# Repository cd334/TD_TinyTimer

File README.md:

# TD_TinyTimer
This is a hardware design for [Phobos Lap Timer](https://github.com/phobos-/PhobosLT)

-----------------------------------------------------------------------
Copyright @ Dániel Czigány 2024.

This source describes Open Hardware and is licensed under the CERN-OHL-P v2

You may redistribute and modify this documentation and make products using it under the terms of the CERN-OHL-P v2 (https:/cern.ch/cern-ohl).
This documentation is distributed WITHOUT ANY EXPRESS OR IMPLIED WARRANTY, INCLUDING OF MERCHANTABILITY, SATISFACTORY QUALITY AND FITNESS FOR A PARTICULAR PURPOSE. Please see the CERN-OHL-P v2 for applicable conditions

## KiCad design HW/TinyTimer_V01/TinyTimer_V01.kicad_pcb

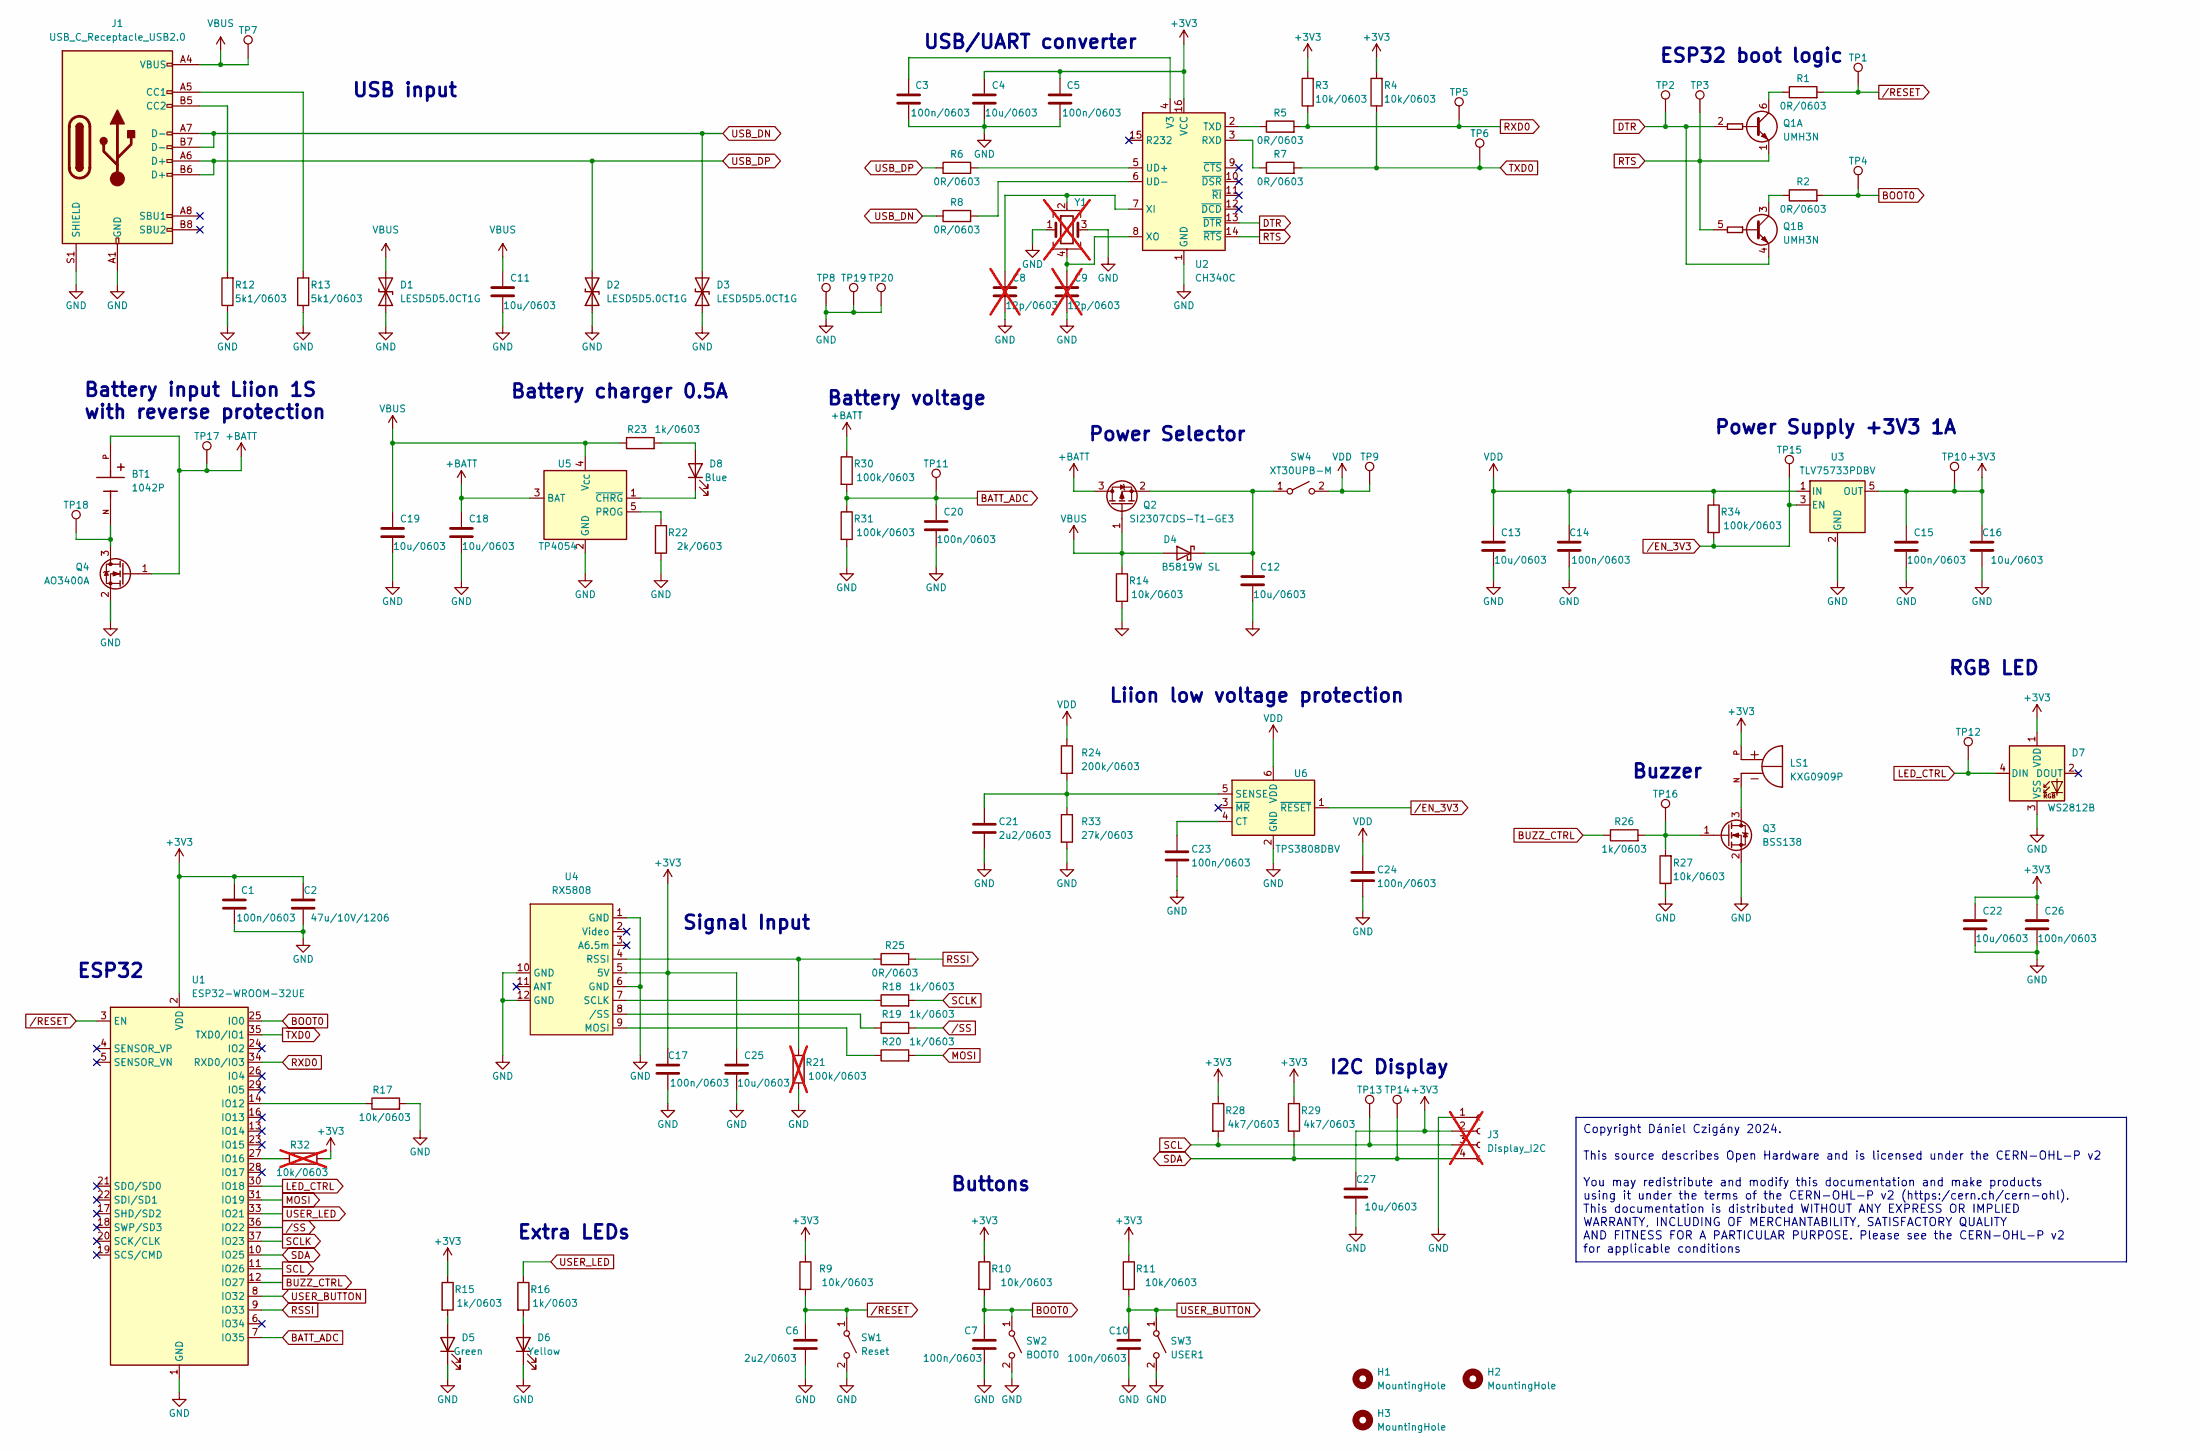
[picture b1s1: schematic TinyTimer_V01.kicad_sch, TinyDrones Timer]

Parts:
BT1: 1042P; BAT_1042P; PARTREV D; LCSC C2988620
C1, C3, C5, C7, C10, C14, C15, C17, C20, C23, C24, C26: 100n/0603; C_0603_1608Metric; LCSC C14663
C2: 47u/10V/1206; C_1206_3216Metric; JLCPCB C96123
C4, C11, C12, C13, C16, C18, C19, C22, C25, C27: 10u/0603; C_0603_1608Metric; LCSC C96446
C6, C21: 2u2/0603; C_0603_1608Metric; LCSC C14663
C8, C9: 12p/0603; C_0603_1608Metric; not fitted
D1, D2, D3: LESD5D5.0CT1G; D_SOD-523; LCSC C383211
D4: B5819W SL; D_SOD-123; LCSC C8598
D5: Green; LED_0603_1608Metric; LCSC C84264
D6: Yellow; LED_0603_1608Metric; LCSC C84265
D7: WS2812B; LED_WS2812B_PLCC4_5.0x5.0mm_P3.2mm; LCSC C2843785
D8: Blue; LED_0603_1608Metric; LCSC C84266
H1, H2, H3: MountingHole; MountingHole_3.5mm
J1: USB_C_Receptacle_USB2.0; USB_C_Receptacle_HRO_TYPE-C-31-M-12; LCSC C2927300
J3: Display_I2C; JST_XH_B4B-XH-A_1x04_P2.50mm_Vertical; not fitted
LS1: KXG0909P; XDCR_KXG0909P; PARTREV 1.1
Q1: UMH3N; SOT-363_SC-70-6; LCSC C62892
Q2: SI2307CDS-T1-GE3; SOT-23; LCSC C141561
Q3: BSS138; SOT-23; LCSC C255592
Q4: AO3400A; SOT-23; LCSC C20917
R1, R2, R5, R6, R7, R8, R25: 0R/0603; R_0603_1608Metric; LCSC C21189
R3, R4, R9, R10, R11, R14, R17, R27: 10k/0603; R_0603_1608Metric; LCSC C25804
R12, R13: 5k1/0603; R_0603_1608Metric; LCSC C23186
R15, R16, R18, R19, R20, R23, R26: 1k/0603; R_0603_1608Metric; LCSC C21190
R21: 100k/0603; R_0603_1608Metric; LCSC C25803; not fitted
R22: 2k/0603; R_0603_1608Metric; LCSC C4190
R24: 200k/0603; R_0603_1608Metric; LCSC C25811
R28, R29: 4k7/0603; R_0603_1608Metric; LCSC C23162
R30, R31, R34: 100k/0603; R_0603_1608Metric; LCSC C25803
R32: 10k/0603; R_0603_1608Metric; LCSC C25804; not fitted
R33: 27k/0603; R_0603_1608Metric; LCSC C22967
SW1: Reset; SW_SPST_B3U-1000P; LCSC C2905189
SW2: BOOT0; SW_SPST_B3U-1000P; LCSC C2905189
SW3: USER1; SW_SPST_B3U-1000P; LCSC C2905189
SW4: XT30UPB-M; PhoenixContact_MCV_1,5_2-G-3.81_1x02_P3.81mm_Vertical
TP1, TP2, TP3, TP4, TP5, TP6, TP7, TP8, TP9, TP10, TP11, TP12, TP13, TP14, TP15, TP16, TP17, TP18: TestPoint; TestPoint_Pad_D1.0mm
TP19, TP20: TestPoint; TestPoint_THTPad_D3.0mm_Drill1.5mm
U1: ESP32-WROOM-32UE; LCSC C701344
U2: CH340C; SOIC-16_3.9x9.9mm_P1.27mm; LCSC C84681
U3: TLV75733PDBV; SOT-23-5; LCSC C485517
U4: RX5808; RX5808_THT
U5: TP4054; TSOT-23-5; LCSC C668215
U6: TPS3808DBV; SOT-23-6; LCSC C19653
Y1: Crystal_GND24; Crystal_SMD_3225-4Pin_3.2x2.5mm; not fitted

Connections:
+3V3: C1.1, C2.1, C4.1, C5.1, C15.1, C16.1, C17.1, C22.1, C25.1, C26.1, C27.1, D7.1 (VDD), J3.2, LS1.P, R3.2, R4.2, R9.1, R10.1, R11.1, R15.1, R28.1, R29.1, R32.2, TP10.1, U1.2 (VDD), U2.16 (VCC), U3.5 (OUT), U4.5 (5V)
+BATT: BT1.P, C18.1, Q2.3 (D), Q4.1 (G), R30.1, TP17.1, U5.3 (BAT)
BATT_ADC: C20.1, R30.2, R31.1, TP11.1, U1.7 (IO35)
BOOT0: C7.1, R2.2, R10.2, SW2.1 (A), TP4.1, U1.25 (IO0)
BUZZ_CTRL: R26.1, U1.12 (IO27)
DTR: Q1.2 (B1), Q1.4 (E2), TP2.1, U2.13 (~DTR)
GND: C1.2, C2.2, C3.2, C4.2, C5.2, C6.2, C7.2, C8.2, C9.2, C10.2, C11.2, C12.2, C13.2, C14.2, C15.2, C16.2, C17.2, C18.2, C19.2, C20.2, C21.2, C22.2, C23.2, C24.2, C25.2, C26.2, C27.2, D1.1 (A1), D2.1 (A1), D3.1 (A1), D5.1 (K), D6.1 (K), D7.3 (VSS), J1.A1 (GND), J1.A12 (GND), J1.B1 (GND), J1.B12 (GND), J1.S1 (SHIELD), J3.1, Q3.2 (S), Q4.2 (S), R12.1, R13.1, R14.2, R17.2, R21.2, R22.2, R27.1, R31.2, R33.2, SW1.2 (B), SW2.2 (B), SW3.2 (B), TP8.1, TP19.1, TP20.1, U1.1 (GND), U1.15 (GND), U1.38 (GND), U1.39 (GND), U2.1 (GND), U3.2 (GND), U4.1 (GND), U4.6 (GND), U4.10 (GND), U4.12 (GND), U5.2 (GND), U6.2 (GND), Y1.1, Y1.3
LED_CTRL: D7.4 (DIN), TP12.1, U1.30 (IO18)
MOSI: R20.2, U1.31 (IO19)
unnamed: C12.1, D4.1 (K), Q2.2 (S), SW4.1 (A)
unnamed: D5.2 (A), R15.2
unnamed: D6.2 (A), R16.2
unnamed: D8.2 (A), R23.2
unnamed: D8.1 (K), U5.1 (~CHRG)
unnamed: J1.A5 (CC1), R13.2
unnamed: J1.B5 (CC2), R12.2
unnamed: Q1.6 (C1), R1.1
unnamed: Q1.3 (C2), R2.1
unnamed: LS1.N, Q3.3 (D)
unnamed: Q3.1 (G), R26.2, R27.2, TP16.1
unnamed: BT1.N, Q4.3 (D), TP18.1
unnamed: R17.1, U1.14 (IO12)
unnamed: R32.1, U1.27 (IO16)
unnamed: R7.1, U2.3 (RXD)
unnamed: R5.1, U2.2 (TXD)
unnamed: R6.2, U2.5 (UD+)
unnamed: R8.2, U2.6 (UD-)
unnamed: C3.1, U2.4 (V3)
unnamed: C8.1, U2.7 (XI), Y1.2
unnamed: C9.1, U2.8 (XO), Y1.4
unnamed: R20.1, U4.9 (MOSI)
unnamed: R21.1, R25.1, U4.4 (RSSI)
unnamed: R18.1, U4.7 (SCLK)
unnamed: R19.1, U4.8 (/SS)
unnamed: R22.1, U5.5 (PROG)
unnamed: C23.1, U6.4 (CT)
unnamed: C21.1, R24.2, R33.1, U6.5 (SENSE)
RSSI: R25.2, U1.9 (IO33)
RTS: Q1.1 (E1), Q1.5 (B2), TP3.1, U2.14 (~RTS)
RXD0: R3.1, R5.2, TP5.1, U1.34 (RXD0/IO3)
SCL: J3.3, R28.2, TP13.1, U1.11 (IO26)
SCLK: R18.2, U1.37 (IO23)
SDA: J3.4, R29.2, TP14.1, U1.10 (IO25)
TXD0: R4.1, R7.2, TP6.1, U1.35 (TXD0/IO1)
USB_DN: D3.2 (A2), J1.A7 (D-), J1.B7 (D-), R8.1
USB_DP: D2.2 (A2), J1.A6 (D+), J1.B6 (D+), R6.1
USER_BUTTON: C10.1, R11.2, SW3.1 (A), U1.8 (IO32)
USER_LED: R16.1, U1.33 (IO21)
VBUS: C11.1, C19.1, D1.2 (A2), D4.2 (A), J1.A4 (VBUS), J1.A9 (VBUS), J1.B4 (VBUS), J1.B9 (VBUS), Q2.1 (G), R14.1, R23.1, TP7.1, U5.4 (V_{CC})
VDD: C13.1, C14.1, C24.1, R24.1, R34.1, SW4.2 (B), TP9.1, U3.1 (IN), U6.6 (VDD)
/EN_3V3: R34.2, TP15.1, U3.3 (EN), U6.1 (~RESET)
/RESET: C6.1, R1.2, R9.2, SW1.1 (A), TP1.1, U1.3 (EN)
/SS: R19.2, U1.36 (IO22)

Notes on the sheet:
Copyright Dániel Czigány 2024. This source describes Open Hardware and is licensed under the CERN-OHL-P v2 You may redistribute and modify this documentation and make products using it under the terms of the CERN-OHL-P v2 (https:/cern.ch/cern-ohl). This documentation is distributed WITHOUT ANY EXPR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
Power Supply +3V3 1A
ESP32
Battery input Liion 1S with reverse protection
USB input
Extra LEDs
Buttons
Battery charger 0.5A
Liion low voltage protection
I2C Display
RGB LED
Buzzer
Battery voltage
Signal Input
USB/UART converter
Power Selector
ESP32 boot logic

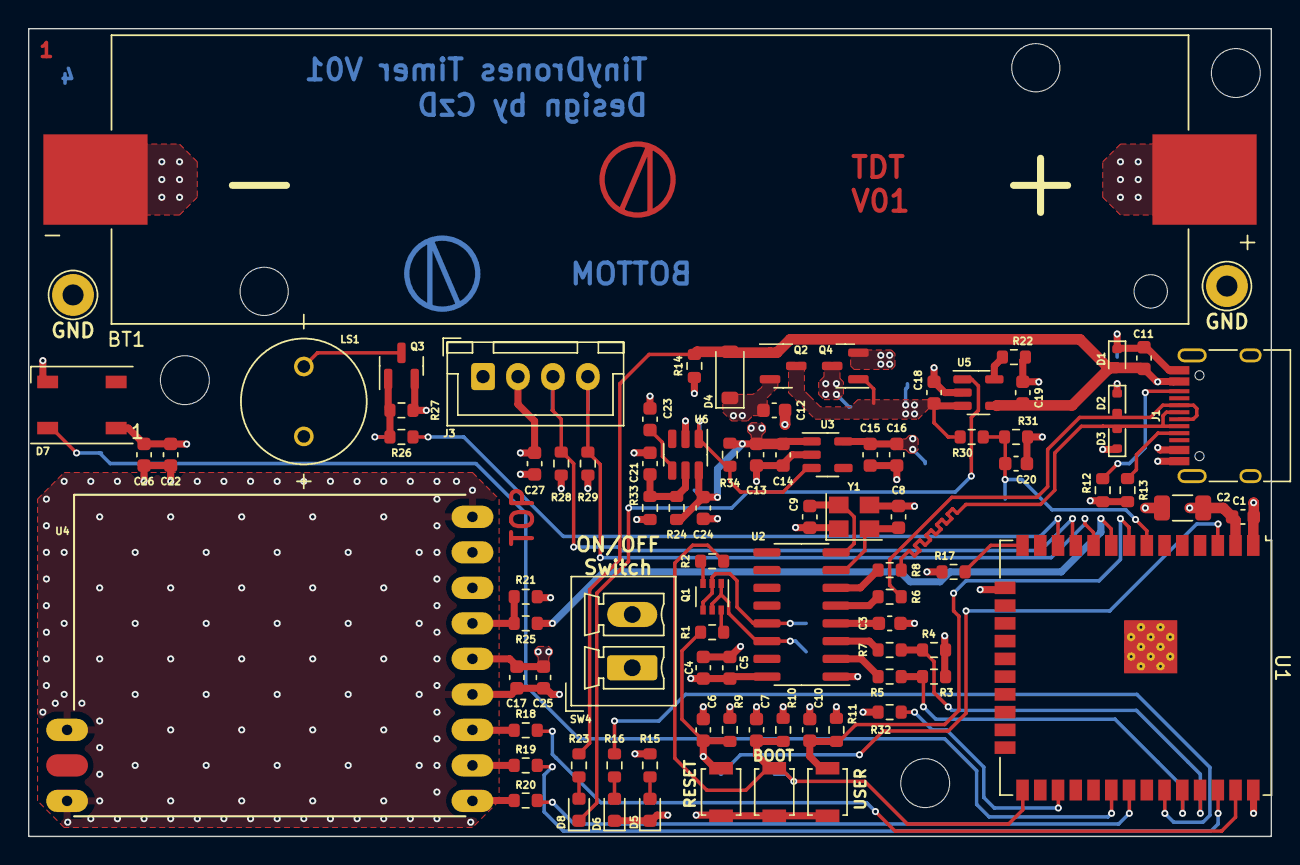
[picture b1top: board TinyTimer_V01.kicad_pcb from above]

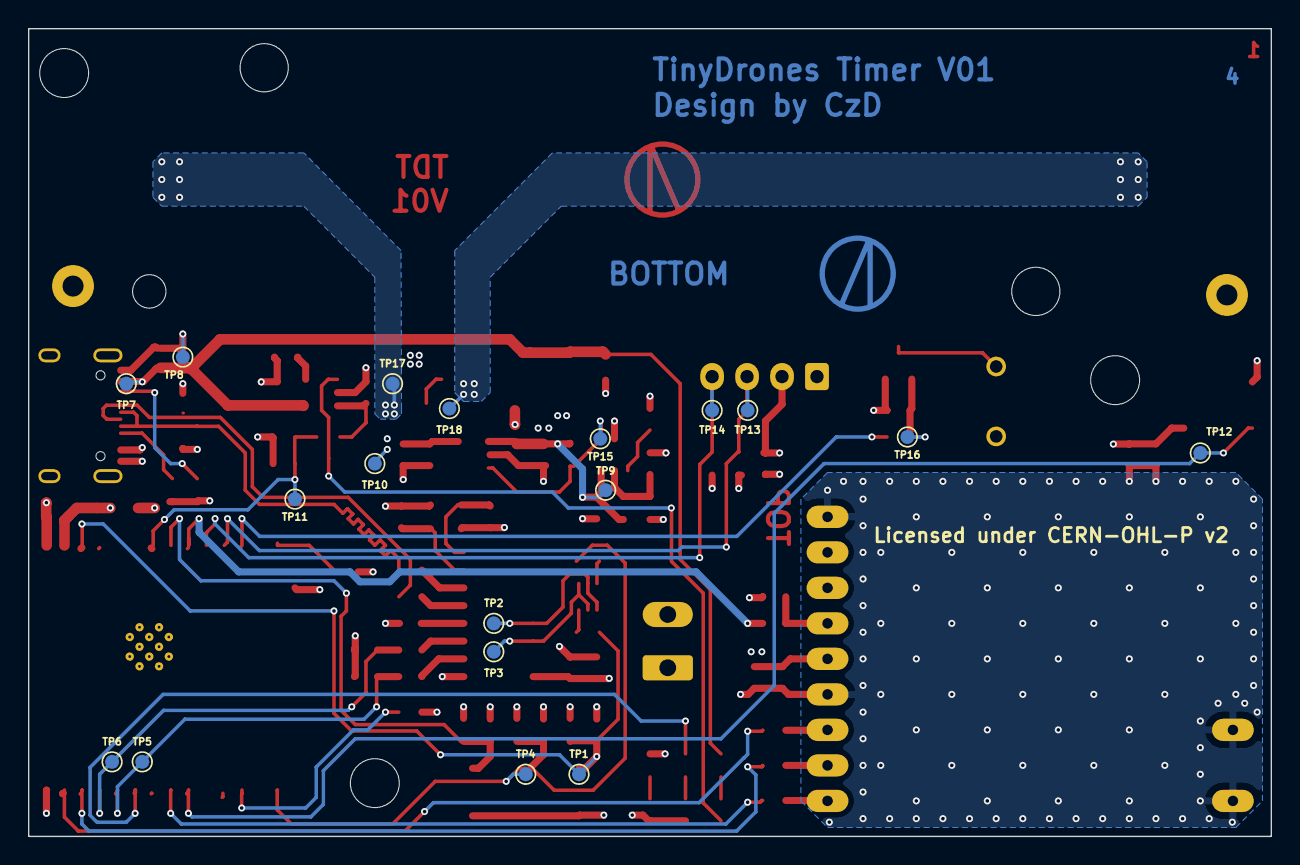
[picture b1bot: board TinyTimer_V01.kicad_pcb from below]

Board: 4 copper layers, 88.9 x 57.8 mm, 111 parts (18 on the bottom side), 53 nets.

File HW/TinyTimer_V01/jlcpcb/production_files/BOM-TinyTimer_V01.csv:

Comment,Designator,Footprint,LCSC,Quantity
SI2307CDS-T1-GE3,Q2,SOT-23,C141561,1
100n/0603,"C1,C10,C14,C15,C17,C20,C21,C23,C24,C26,C3,C5,C6,C7",C_0603_1608Metric,C14663,14
TPS3808DBV,U6,SOT-23-6,C19653,1
AO3400A,Q4,SOT-23,C20917,1
0R/0603,"R1,R2,R25,R5,R6,R7,R8",R_0603_1608Metric,C21189,7
1k/0603,"R15,R16,R18,R19,R20,R23,R26",R_0603_1608Metric,C21190,7
27k/0603,R33,R_0603_1608Metric,C22967,1
4k7/0603,"R28,R29",R_0603_1608Metric,C23162,2
5k1/0603,"R12,R13",R_0603_1608Metric,C23186,2
BSS138,Q3,SOT-23,C255592,1
100k/0603,"R21,R30,R31,R34",R_0603_1608Metric,C25803,4
10k/0603,"R10,R11,R14,R17,R27,R3,R4,R9",R_0603_1608Metric,C25804,8
200k/0603,R24,R_0603_1608Metric,C25811,1
WS2812B,D7,LED_WS2812B_PLCC4_5.0x5.0mm_P3.2mm,C2843785,1
Reset,"SW1,SW2,SW3",SW_SPST_B3U-1000P,C2905189,3
USB_C_Receptacle_USB2.0,J1,USB_C_Receptacle_HRO_TYPE-C-31-M-12,C2927300,1
1042P,BT1,BAT_1042P,C2988620,1
LESD5D5.0CT1G,"D1,D2,D3",D_SOD-523,C383211,3
2k/0603,R22,R_0603_1608Metric,C4190,1
TLV75733PDBV,U3,SOT-23-5,C485517,1
UMH3N,Q1,SOT-363_SC-70-6,C62892,1
TP4054,U5,TSOT-23-5,C668215,1
ESP32-WROOM-32UE,U1,ESP32-WROOM-32UE,C701344,1
Green,D5,LED_0603_1608Metric,C84264,1
Yellow,D6,LED_0603_1608Metric,C84265,1
Blue,D8,LED_0603_1608Metric,C84266,1
CH340C,U2,SOIC-16_3.9x9.9mm_P1.27mm,C84681,1
B5819W SL,D4,D_SOD-123,C8598,1
47u/10V/1206,C2,C_1206_3216Metric,C96123,1
10u/0603,"C11,C12,C13,C16,C18,C19,C22,C25,C27,C4",C_0603_1608Metric,C96446,10

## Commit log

2024-11-13 Update README.md
    Start working with the repository
    Updated README.md
2024-11-18 Initial commit of the HW
    This is the initial commit of the KiCAD project, the JLCPCB production files and case

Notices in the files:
HW/TinyTimer_V01/TinyTimer_V01.kicad_pcb:
Licensed under CERN-OHL-P v2
